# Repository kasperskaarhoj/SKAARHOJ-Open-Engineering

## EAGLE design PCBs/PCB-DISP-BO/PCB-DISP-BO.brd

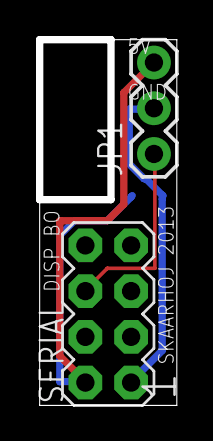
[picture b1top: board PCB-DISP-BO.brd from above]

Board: 2 copper layers, 7.6 x 20.3 mm, 3 parts (1 on the bottom side), 3 nets.

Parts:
C1: 10uF; 0603-CAP
JP1: 1X03
SERIAL: M04X2; 2X4

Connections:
5V: C1.1, JP1.3, SERIAL.2
DISP_DATA_OUT: JP1.1, SERIAL.6
GND: C1.2, JP1.2, SERIAL.1

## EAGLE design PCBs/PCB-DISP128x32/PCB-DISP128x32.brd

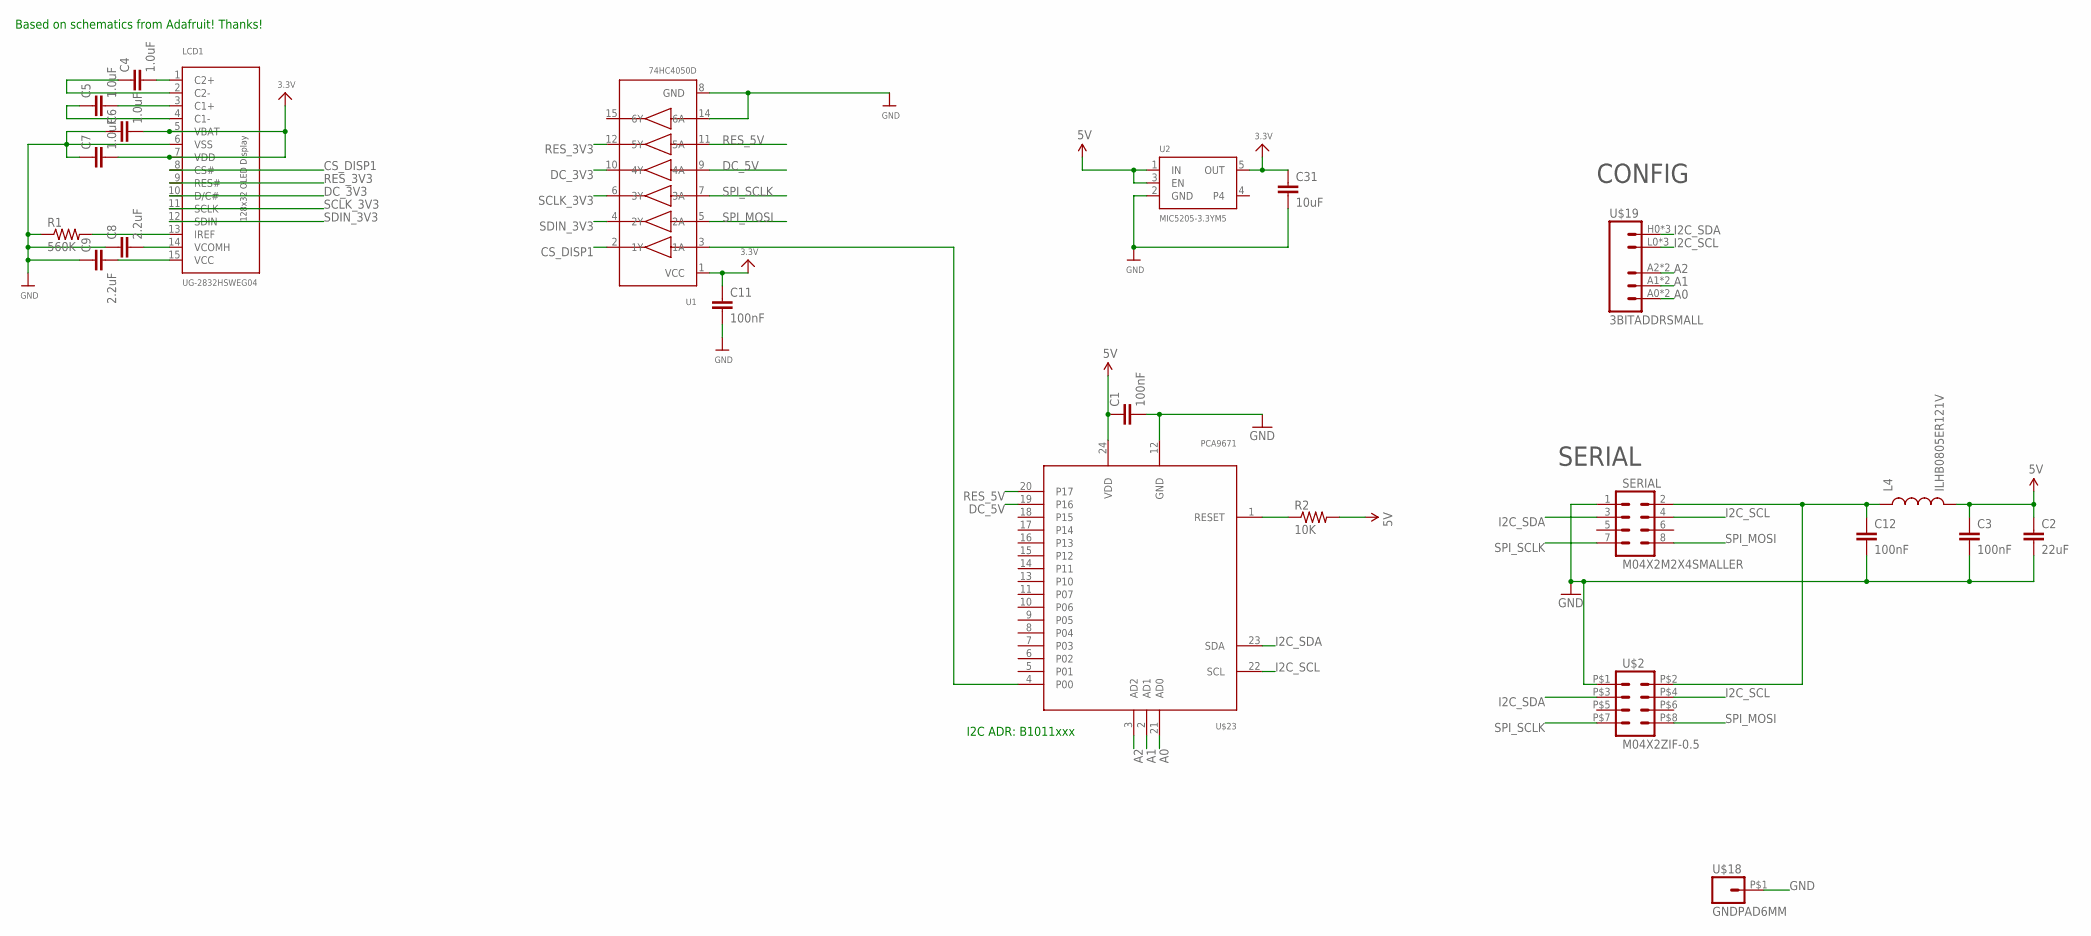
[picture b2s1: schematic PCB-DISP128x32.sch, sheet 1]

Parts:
C1, C3, C11, C12: 100nF; 0603-CAP
C2: 22uF; 0805
C4, C5, C6, C7: 1.0uF; 0603-CAP
C8, C9: 2.2uF; 0603-CAP
C31: 10uF; 0805
L4: ILHB0805ER121V; 0805
LCD1: UG-2832HSWEG04; UG-2832HSWEG04_WRAPAROUND
R1: 560K; 0603-RES
R2: 10K; 0603-RES
SERIAL: M04X2M2X4SMALLER; M2X4SMALLER
U1: 74HC4050D; TSSOP16
U2: MIC5205-3.3YM5; SOT23-5
U$2: M04X2ZIF-0.5; ZIP-8-0.5
U$18: GNDPAD6MM; 3.2MMPAD6MM
U$19: 3BITADDRSMALL; 3BITADDR_SMALL
U$23: PCA9671; TSSOP24

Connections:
3.3V: C6.2, C7.2, C11.1, C31.1, LCD1.5 (VBAT), LCD1.7 (VDD), U1.1 (VCC), U2.5 (OUT)
5V: C1.1, C2.1, C3.1, L4.2, R2.2, U2.1 (IN), U2.3 (EN), U$23.24 (VDD)
A0: U$19.A0, U$19.AS0 (A0), U$23.21 (AD0)
A1: U$19.A1, U$19.AS1 (A1), U$23.2 (AD1)
A2: U$19.A2, U$19.AS2 (A2), U$23.3 (AD2)
ARD_5V: C12.1, L4.1, SERIAL.2, U$2.P$2 (2)
CS_DISP1: LCD1.8 (CS#), U1.2 (1Y)
DC_3V3: LCD1.10 (D/C#), U1.10 (4Y)
DC_5V: U1.9 (4A), U$23.19 (P16)
GND: C1.2, C2.2, C3.2, C6.1, C7.1, C8.1, C9.1, C11.2, C12.2, C31.2, LCD1.6 (VSS), R1.1, SERIAL.1, U1.8 (GND), U1.14 (6A), U2.2 (GND), U$2.P$1 (1), U$18.P$1, U$23.12 (GND)
I2C_SCL: SERIAL.4, U$2.P$4 (4), U$19.L0 (GND), U$19.L1 (GND), U$19.L2 (GND), U$23.22 (SCL)
I2C_SDA: SERIAL.3, U$2.P$3 (3), U$19.H0 (VCC), U$19.H1 (VCC), U$19.H2 (VCC), U$23.23 (SDA)
unnamed: R2.1, U$23.1 (RESET)
unnamed: C4.1, LCD1.2 (C2-)
unnamed: C4.2, LCD1.1 (C2+)
unnamed: C5.1, LCD1.4 (C1-)
unnamed: U1.3 (1A), U$23.4 (P00)
unnamed: C5.2, LCD1.3 (C1+)
unnamed: LCD1.13 (IREF), R1.2
unnamed: C8.2, LCD1.14 (VCOMH)
unnamed: C9.2, LCD1.15 (VCC)
RES_3V3: LCD1.9 (RES#), U1.12 (5Y)
RES_5V: U1.11 (5A), U$23.20 (P17)
SCLK_3V3: LCD1.11 (SCLK), U1.6 (3Y)
SDIN_3V3: LCD1.12 (SDIN), U1.4 (2Y)
SPI_MOSI: SERIAL.8, U1.5 (2A), U$2.P$8 (8)
SPI_SCLK: SERIAL.7, U1.7 (3A), U$2.P$7 (7)

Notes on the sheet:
I2C ADR: B1011xxx
SERIAL
CONFIG
Based on schematics from Adafruit! Thanks!

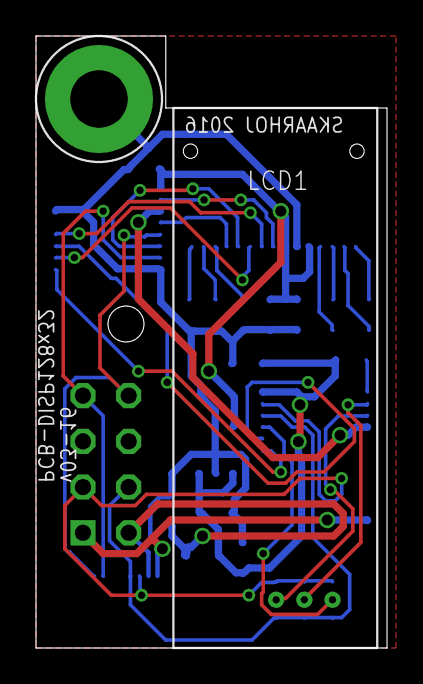
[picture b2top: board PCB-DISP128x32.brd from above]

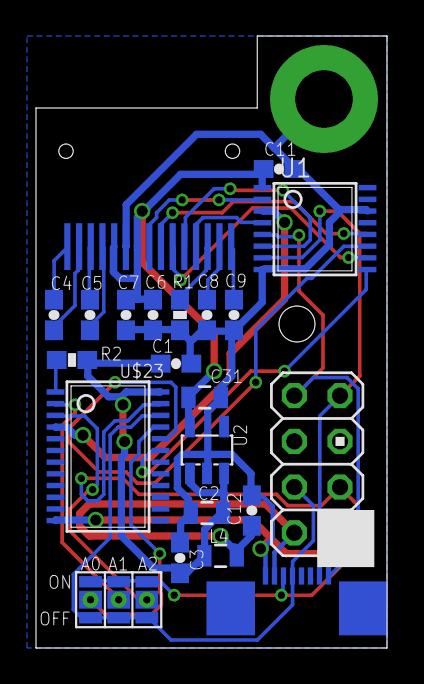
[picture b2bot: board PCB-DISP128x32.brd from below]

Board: 2 copper layers, 19.5 x 34.0 mm, 23 parts (21 on the bottom side), 27 nets.

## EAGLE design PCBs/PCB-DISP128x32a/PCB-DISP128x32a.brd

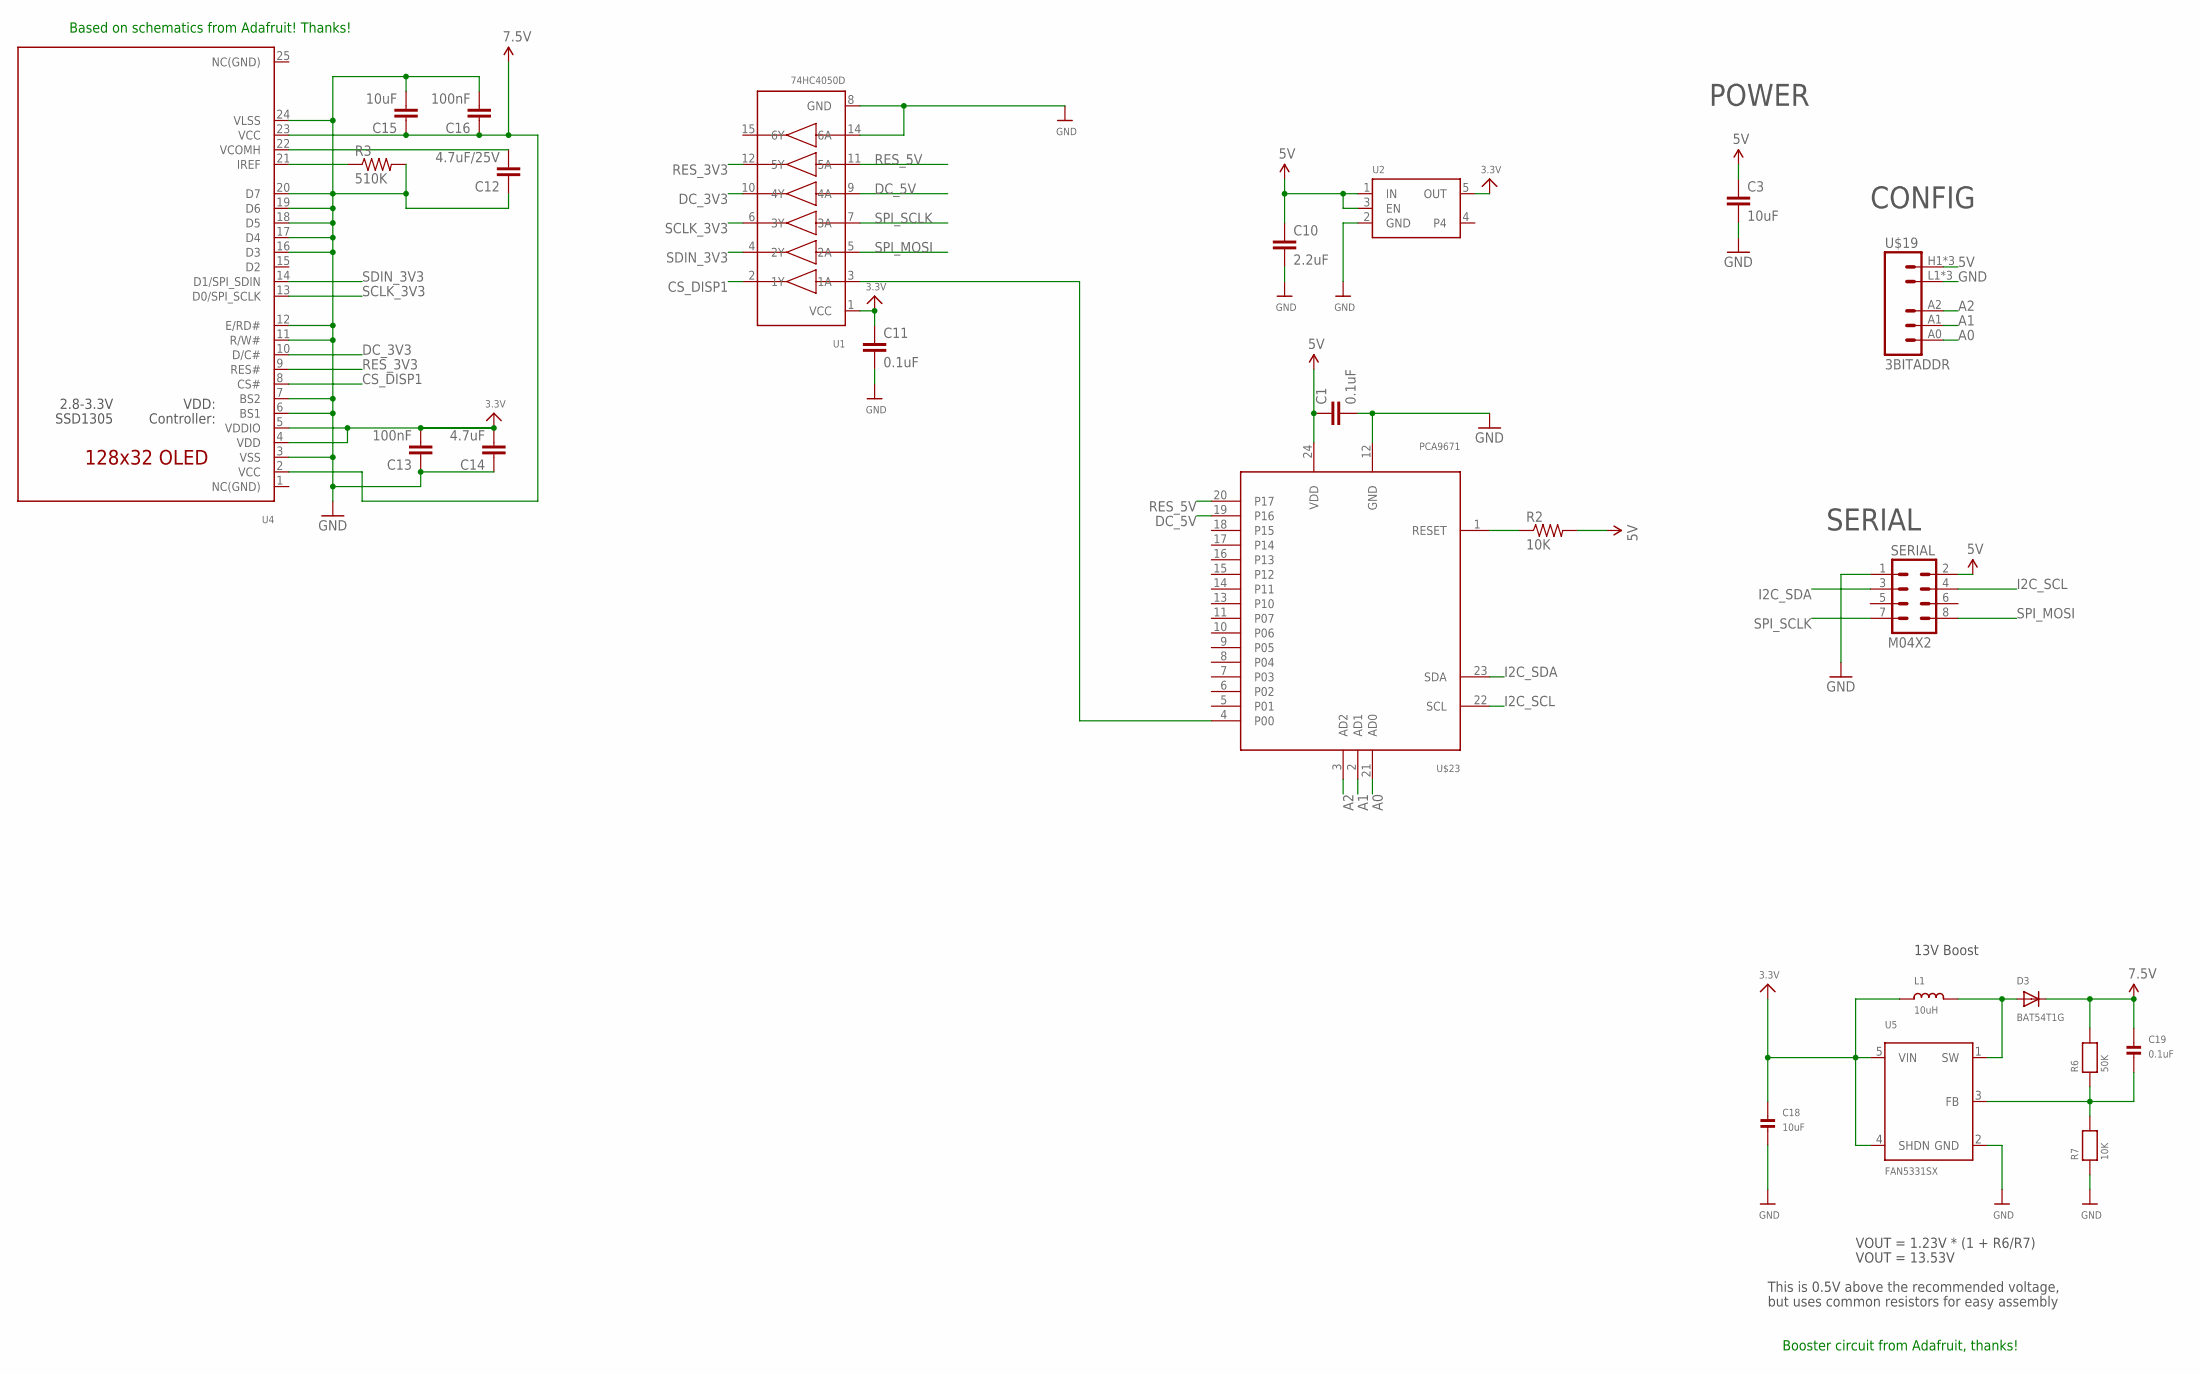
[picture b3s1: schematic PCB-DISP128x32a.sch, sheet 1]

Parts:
C1, C11: 0.1uF; 0603-CAP
C3, C18: 10uF; 0805
C10: 2.2uF; 0603-CAP
C12: 4.7uF/25V; 0805
C13, C16: 100nF; 0603-CAP
C14: 4.7uF; 0603-CAP
C15: 10uF; 0603-CAP
C19: 0.1uF; 0805
D3: BAT54T1G; SOD-123
L1: 10uH; INDUCTOR_1007
R2: 10K; 0603-RES
R3: 510K; 0603-RES
R6: 50K; 0805
R7: 10K; 0805
SERIAL: M04X2; 2X4
U1: 74HC4050D; SOIC16
U2: VREG_SOT23-5; SOT23-5
U4: ER-OLED0.91-2; ER-OLED0.91-2_WRAPAROUND
U5: FAN5331SX; SOT23-5
U$19: 3BITADDR
U$23: PCA9671; TSSOP24

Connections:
3.3V: C11.1, C13.2, C14.2, C18.1, L1.P$1 (1), U1.1 (VCC), U2.5 (OUT), U4.4 (VDD), U4.5 (VDDIO), U5.4 (SHDN), U5.5 (VIN)
5V: C1.1, C3.1, C10.1, R2.2, SERIAL.2, U2.1 (IN), U2.3 (EN), U$19.H1 (VCC), U$19.H2 (VCC), U$19.H3 (VCC), U$23.24 (VDD)
7.5V: C15.1, C16.1, C19.1, D3.C, R6.2, U4.2 (VCC), U4.23 (VCC)
A0: U$19.A0, U$23.21 (AD0)
A1: U$19.A1, U$23.2 (AD1)
A2: U$19.A2, U$23.3 (AD2)
CS_DISP1: U1.2 (1Y), U4.8 (CS#)
DC_3V3: U1.10 (4Y), U4.10 (D/C#)
DC_5V: U1.9 (4A), U$23.19 (P16)
GND: C1.2, C3.2, C10.2, C11.2, C12.1, C13.1, C14.1, C15.2, C16.2, C18.2, R3.2, R7.1, SERIAL.1, U1.8 (GND), U1.14 (6A), U2.2 (GND), U4.3 (VSS), U4.6 (BS1), U4.7 (BS2), U4.11 (R/W#), U4.12 (E/RD#), U4.16 (D3), U4.17 (D4), U4.18 (D5), U4.19 (D6), U4.20 (D7), U4.24 (VLSS), U5.2 (GND), U$19.L1 (GND), U$19.L2 (GND), U$19.L3 (GND), U$23.12 (GND)
I2C_SCL: SERIAL.4, U$23.22 (SCL)
I2C_SDA: SERIAL.3, U$23.23 (SDA)
unnamed: R2.1, U$23.1 (RESET)
unnamed: U1.3 (1A), U$23.4 (P00)
unnamed: R3.1, U4.21 (IREF)
unnamed: C12.2, U4.22 (VCOMH)
unnamed: D3.A, L1.P$2 (2), U5.1 (SW)
unnamed: C19.2, R6.1, R7.2, U5.3 (FB)
RES_3V3: U1.12 (5Y), U4.9 (RES#)
RES_5V: U1.11 (5A), U$23.20 (P17)
SCLK_3V3: U1.6 (3Y), U4.13 (D0/SPI_SCLK)
SDIN_3V3: U1.4 (2Y), U4.14 (D1/SPI_SDIN)
SPI_MOSI: SERIAL.8, U1.5 (2A)
SPI_SCLK: SERIAL.7, U1.7 (3A)

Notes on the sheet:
SERIAL
POWER
CONFIG
Based on schematics from Adafruit! Thanks!
VOUT = 1.23V * (1 + R6/R7)
VOUT = 13.53V
This is 0.5V above the recommended voltage,
but uses common resistors for easy assembly
13V Boost
Booster circuit from Adafruit, thanks!

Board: 2 copper layers, 24 parts (23 on the bottom side), 24 nets, no tracks yet.

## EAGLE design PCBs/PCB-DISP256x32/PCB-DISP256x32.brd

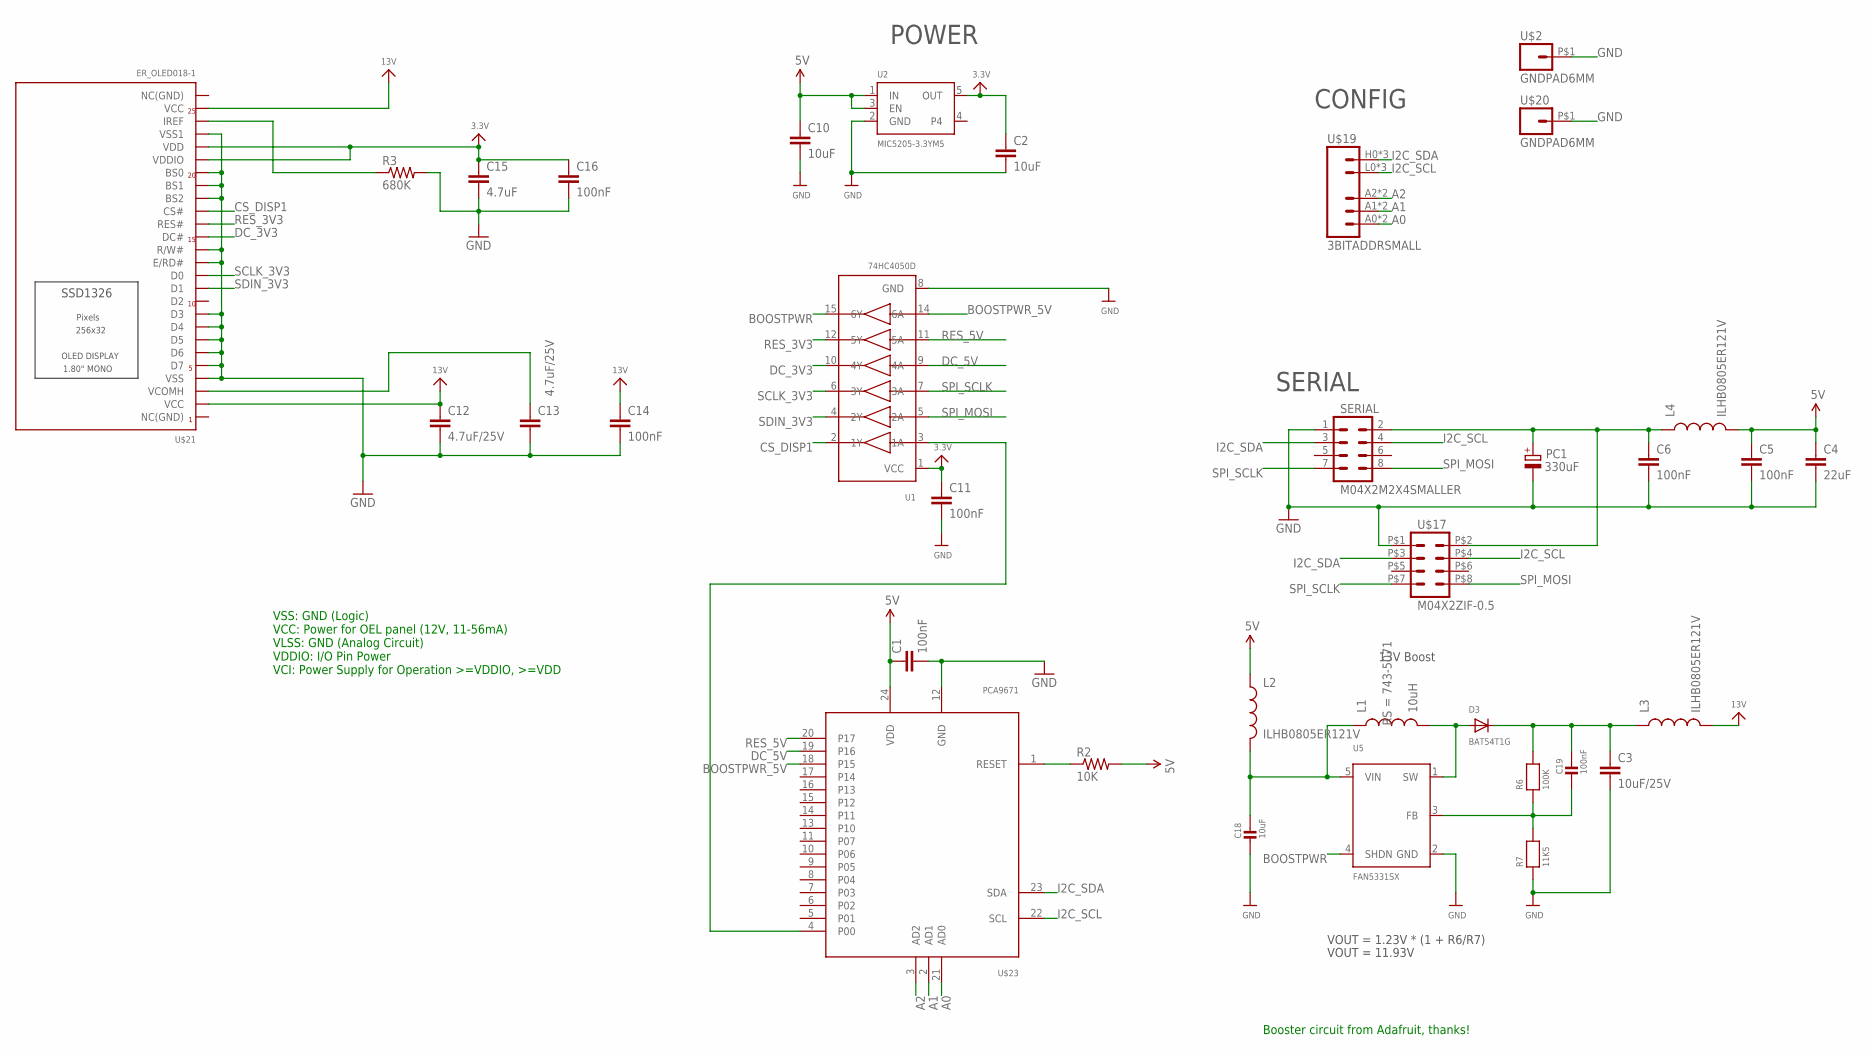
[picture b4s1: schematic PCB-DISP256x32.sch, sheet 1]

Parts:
C1, C5, C6, C11, C14, C16: 100nF; 0603-CAP
C2, C10, C18: 10uF; 0805
C3: 10uF/25V; 0805
C4: 22uF; 0805
C12, C13: 4.7uF/25V; 0805
C15: 4.7uF; 0805
C19: 100nF; 0603
D3: BAT54T1G; SOD-123
L1: 10uH; 3015
L2, L3, L4: ILHB0805ER121V; 0805
PC1: 330uF; PANASONIC_D
R2: 10K; 0603-RES
R3: 680K; 0603-RES
R6: 100K; 0603
R7: 11K5; 0603
SERIAL: M04X2M2X4SMALLER; M2X4SMALLER
U1: 74HC4050D; TSSOP16
U2: MIC5205-3.3YM5; SOT23-5
U5: FAN5331SX; SOT23-5@1
U$2, U$20: GNDPAD6MM; 3.2MMPAD6MM
U$17: M04X2ZIF-0.5; ZIP-8-0.5
U$19: 3BITADDRSMALL; 3BITADDR_SMALL
U$21: ER_OLED018-1; FH12A-26S-0.5SH(55)
U$23: PCA9671; TSSOP24

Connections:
3.3V: C2.1, C11.1, C15.1, C16.1, U1.1 (VCC), U2.5 (OUT), U$21.P$5 (VDD), U$21.P$6 (VDDIO)
5V: C1.1, C4.1, C5.1, C10.1, L2.1, L4.2, R2.2, U2.1 (IN), U2.3 (EN), U$23.24 (VDD)
13V: C12.1, C14.1, L3.2, U$21.P$2 (VCC), U$21.P$25 (VCC)
A0: U$19.A0, U$19.AS0 (A0), U$23.21 (AD0)
A1: U$19.A1, U$19.AS1 (A1), U$23.2 (AD1)
A2: U$19.A2, U$19.AS2 (A2), U$23.3 (AD2)
ARD_5V: C6.1, L4.1, PC1.+, SERIAL.2, U$17.P$2 (2)
BOOSTPWR: U1.15 (6Y), U5.4 (SHDN)
BOOSTPWR_5V: U1.14 (6A), U$23.18 (P15)
CS_DISP1: U1.2 (1Y), U$21.P$10 (CS#)
DC_3V3: U1.10 (4Y), U$21.P$12 (DC#)
DC_5V: U1.9 (4A), U$23.19 (P16)
GND: C1.2, C2.2, C3.2, C4.2, C5.2, C6.2, C10.2, C11.2, C12.2, C13.2, C14.2, C15.2, C16.2, C18.2, PC1.-, R3.2, R7.1, SERIAL.1, U1.8 (GND), U2.2 (GND), U5.2 (GND), U$2.P$1, U$17.P$1 (1), U$20.P$1, U$21.P$4 (VSS1), U$21.P$7 (BS0), U$21.P$8 (BS1), U$21.P$9 (BS2), U$21.P$13 (R/W#), U$21.P$14 (E/RD#), U$21.P$18 (D3), U$21.P$19 (D4), U$21.P$20 (D5), U$21.P$21 (D6), U$21.P$22 (D7), U$21.P$23 (VSS), U$23.12 (GND)
I2C_SCL: SERIAL.4, U$17.P$4 (4), U$19.L0 (GND), U$19.L1 (GND), U$19.L2 (GND), U$23.22 (SCL)
I2C_SDA: SERIAL.3, U$17.P$3 (3), U$19.H0 (VCC), U$19.H1 (VCC), U$19.H2 (VCC), U$23.23 (SDA)
unnamed: R2.1, U$23.1 (RESET)
unnamed: C18.1, L1.1, L2.2, U5.5 (VIN)
unnamed: U1.3 (1A), U$23.4 (P00)
unnamed: C3.1, C19.1, D3.C, L3.1, R6.2
unnamed: C13.1, U$21.P$24 (VCOMH)
unnamed: R3.1, U$21.P$3 (IREF)
unnamed: D3.A, L1.2, U5.1 (SW)
unnamed: C19.2, R6.1, R7.2, U5.3 (FB)
RES_3V3: U1.12 (5Y), U$21.P$11 (RES#)
RES_5V: U1.11 (5A), U$23.20 (P17)
SCLK_3V3: U1.6 (3Y), U$21.P$15 (D0)
SDIN_3V3: U1.4 (2Y), U$21.P$16 (D1)
SPI_MOSI: SERIAL.8, U1.5 (2A), U$17.P$8 (8)
SPI_SCLK: SERIAL.7, U1.7 (3A), U$17.P$7 (7)

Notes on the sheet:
SERIAL
POWER
CONFIG
VOUT = 1.23V * (1 + R6/R7)
VOUT = 11.93V
13V Boost
Booster circuit from Adafruit, thanks!
VSS: GND (Logic) VCC: Power for OEL panel (12V, 11-56mA) VLSS: GND (Analog Circuit) VDDIO: I/O Pin Power VCI: Power Supply for Operation >=VDDIO, >=VDD

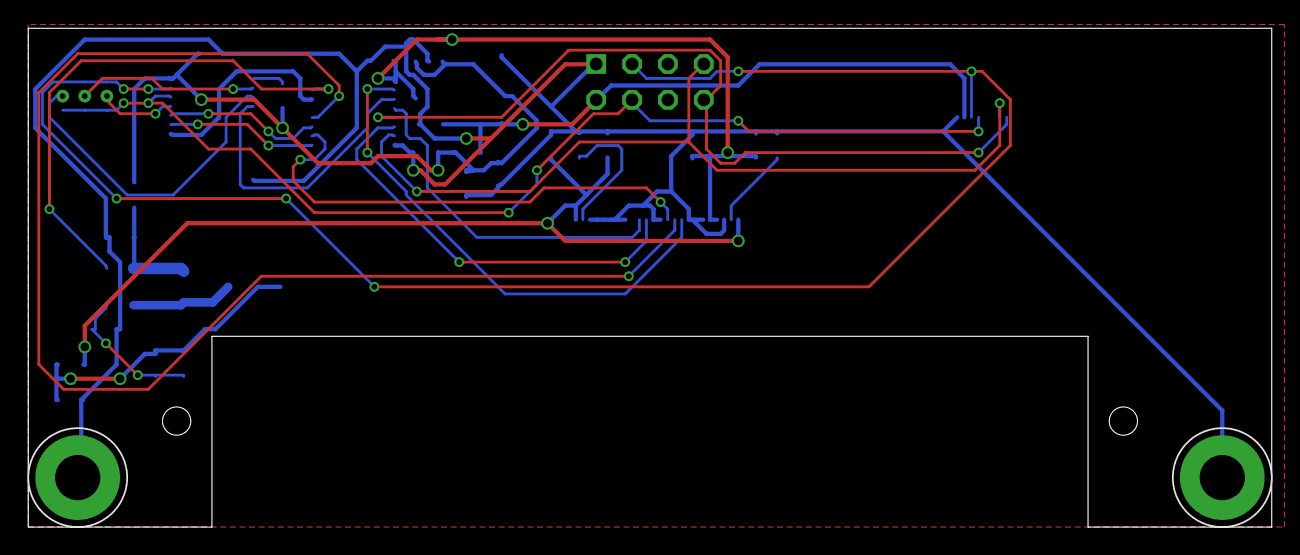
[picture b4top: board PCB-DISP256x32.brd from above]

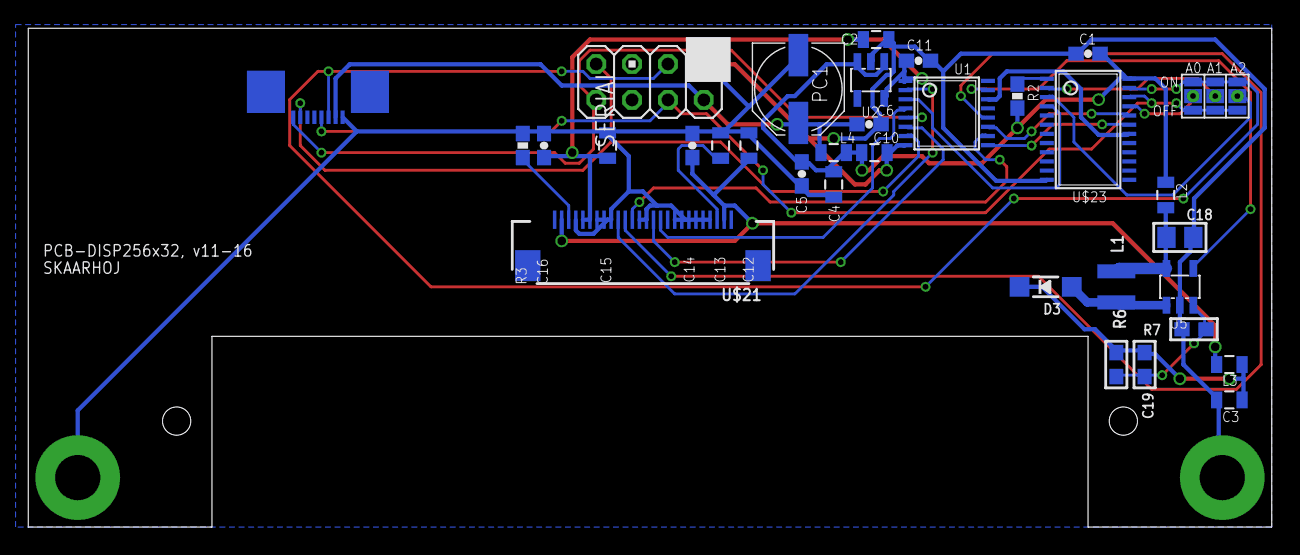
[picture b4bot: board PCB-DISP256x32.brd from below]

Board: 2 copper layers, 88.0 x 35.3 mm, 35 parts (33 on the bottom side), 29 nets.

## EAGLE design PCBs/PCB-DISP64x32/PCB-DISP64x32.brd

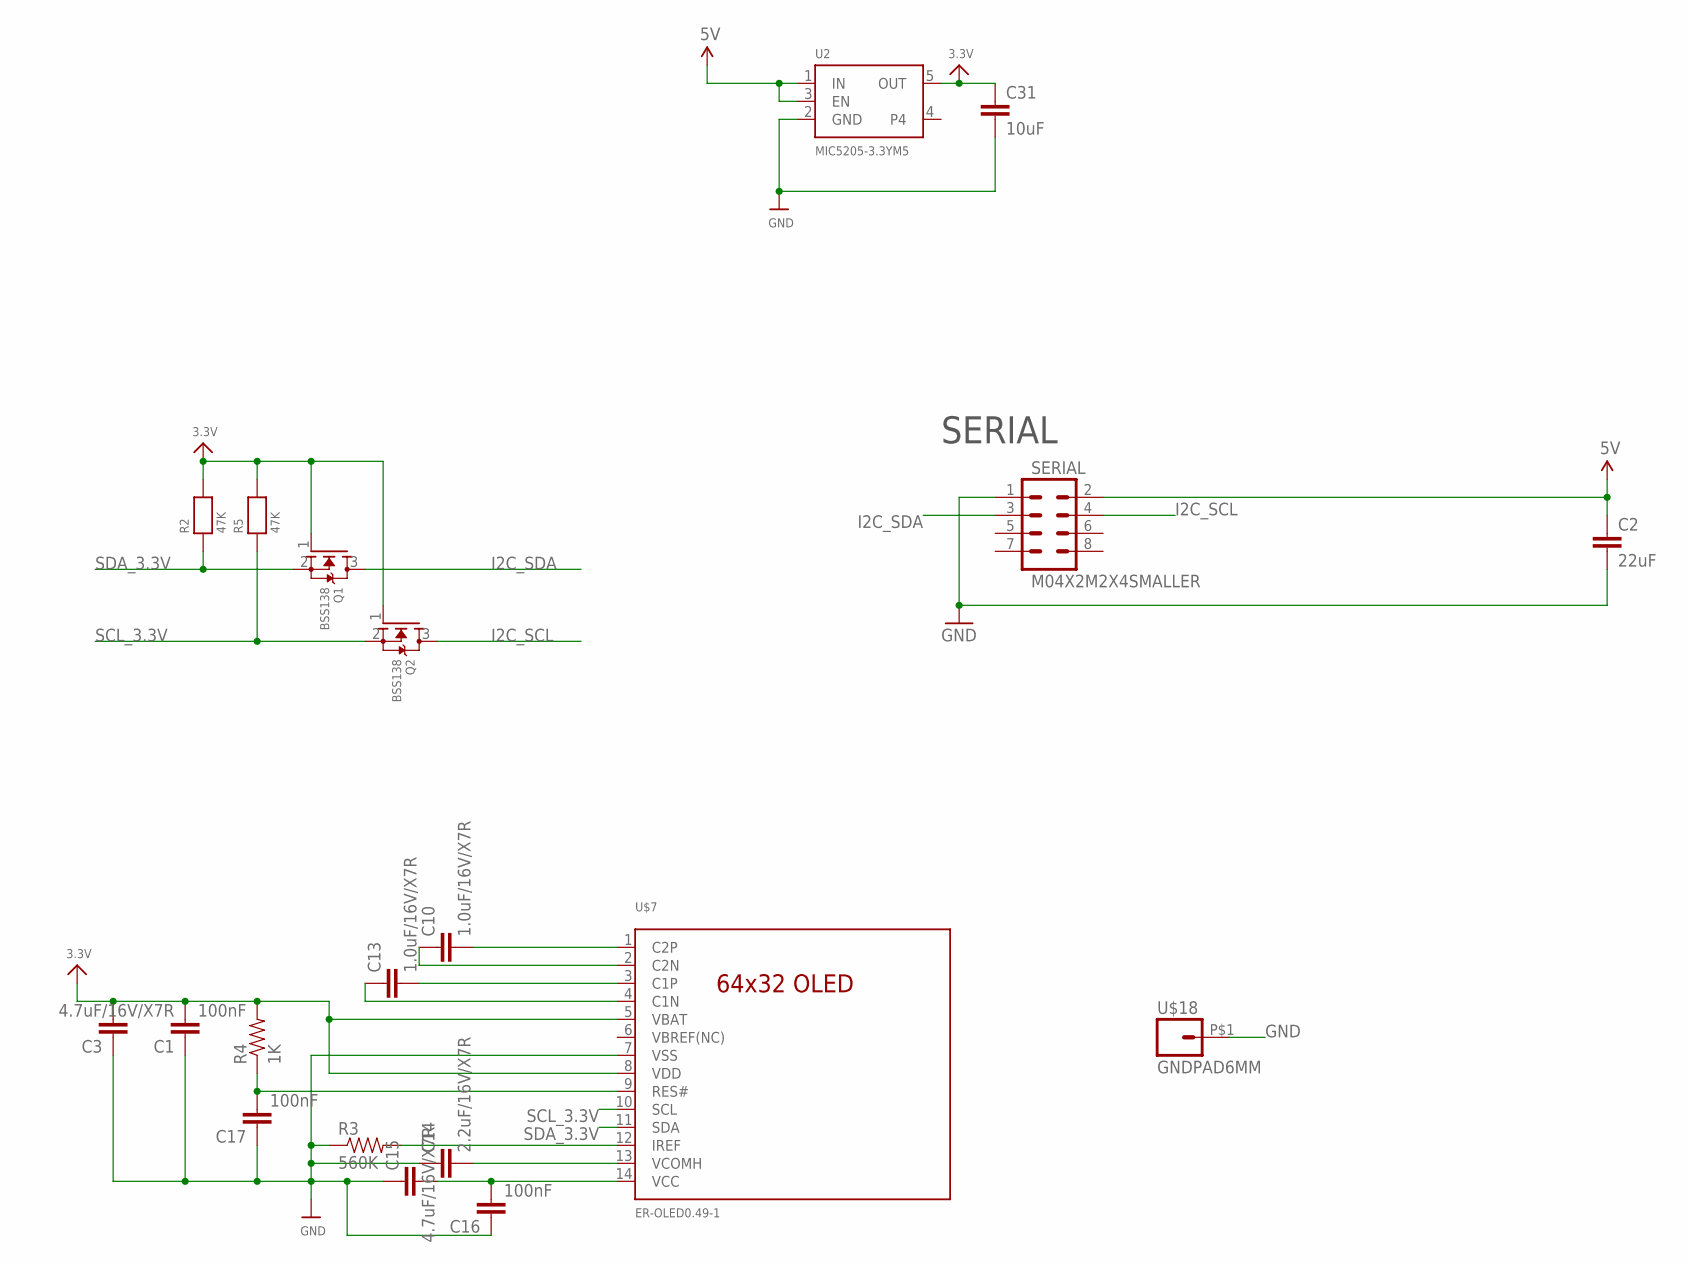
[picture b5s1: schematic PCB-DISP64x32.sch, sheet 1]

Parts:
C1, C16, C17: 100nF; 0603-CAP
C2: 22uF; 0805
C3, C15: 4.7uF/16V/X7R; 0603-CAP
C10, C13: 1.0uF/16V/X7R; 0603-CAP
C14: 2.2uF/16V/X7R; 0603-CAP
C31: 10uF; 0805
Q1, Q2: BSS138; SOT23-R
R2, R5: 47K; 0603
R3: 560K; 0603-RES
R4: 1K; 0603-RES
SERIAL: M04X2M2X4SMALLER; M2X4SMALLER
U2: MIC5205-3.3YM5; SOT23-5
U$7: ER-OLED0.49-1; ER-OLED0.49-1_WRAPAROUND
U$18: GNDPAD6MM; 3.2MMPAD6MM

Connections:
3.3V: C1.2, C3.2, C31.1, Q1.1 (G), Q2.1 (G), R2.2, R4.2, R5.2, U2.5 (OUT), U$7.5 (VBAT), U$7.8 (VDD)
5V: C2.1, SERIAL.2, U2.1 (IN), U2.3 (EN)
GND: C1.1, C2.2, C3.1, C14.1, C15.1, C16.1, C17.1, C31.2, R3.1, SERIAL.1, U2.2 (GND), U$7.7 (VSS), U$18.P$1
I2C_SCL: Q2.3 (D), SERIAL.4
I2C_SDA: Q1.3 (D), SERIAL.3
unnamed: C10.2, U$7.1 (C2P)
unnamed: C13.2, U$7.3 (C1P)
unnamed: C13.1, U$7.4 (C1N)
unnamed: C10.1, U$7.2 (C2N)
unnamed: R3.2, U$7.12 (IREF)
unnamed: C14.2, U$7.13 (VCOMH)
unnamed: C15.2, C16.2, U$7.14 (VCC)
unnamed: C17.2, R4.1, U$7.9 (RES#)
SCL_3.3V: Q2.2 (S), R5.1, U$7.10 (SCL)
SDA_3.3V: Q1.2 (S), R2.1, U$7.11 (SDA)

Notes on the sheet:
SERIAL

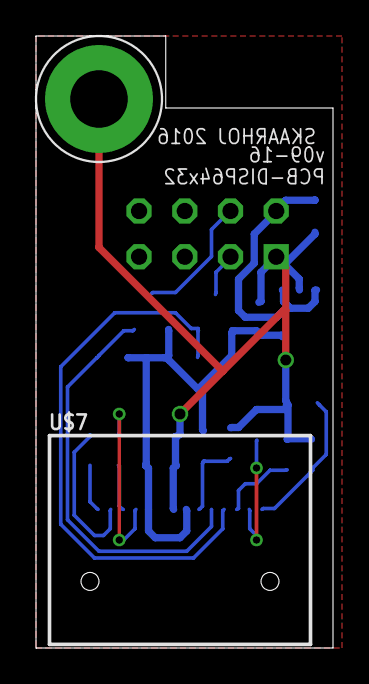
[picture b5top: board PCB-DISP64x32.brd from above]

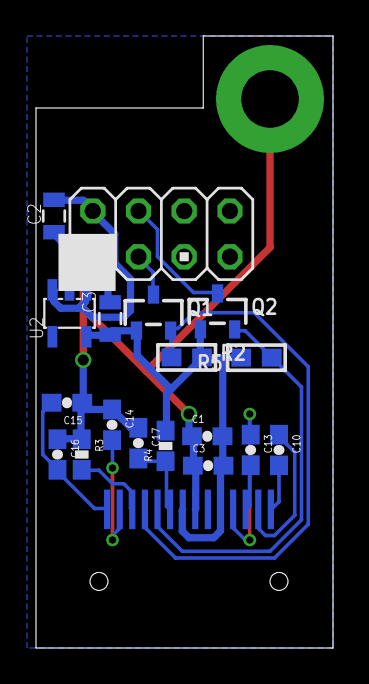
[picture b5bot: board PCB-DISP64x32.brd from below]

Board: 2 copper layers, 16.5 x 34.0 mm, 20 parts (18 on the bottom side), 15 nets.

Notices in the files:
parts and their libraries:
SparkFun: Licensing: CC v3.0 Share-Alike You are welcome to use this library for commercial purposes.
